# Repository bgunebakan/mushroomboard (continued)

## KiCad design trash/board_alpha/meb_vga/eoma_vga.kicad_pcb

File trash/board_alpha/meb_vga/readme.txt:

http://www.gplsquared.com/eoma_boot/vga_2013_08_18.tar.gz

This is to create a VGA interface for EOMA68 Micro Engineering Board

The creative designs here are subject to copyright (C) J. Michael 2013,
and contributors, and all released under GPL 3 license.
You can obtain a copy of the license from http://www.fsf.org

The PCB has been done up for Seeed Studio manufacturing requirements.
There is also eoma_vga_panel.kicad_pcb which has 4 panelized copies inside
a 10cm x 10cm boundary to suit Seeed Studio manufacturing.

If you make a board I'm happy to put put it up as an example board that
others have made.
Send photo by email to research@enemygadgets.com.

Bug fixes for this release:
1. VGA footprint hole diamters to 30 mil
2. SMD electrolytic capacitor 3D orientation repaired
3. Added extra capacitors for decoupling VAA line
4. Added a filter network to power line to prevent RF leaking out that way.
5. Added 1206 ferrite beads (use any off the shelf 1206 size ferrite bead).
6. Repaired wiring for Vref, SYNC and BLANK and got rid of some components.
7. Reparied wiring for VGA gnd connection.
8. Rewired parts of the DIL 22x2 connector.

Previous version :  http://www.gplsquared.com/eoma_boot/vga_2013_08_18.tar.gz

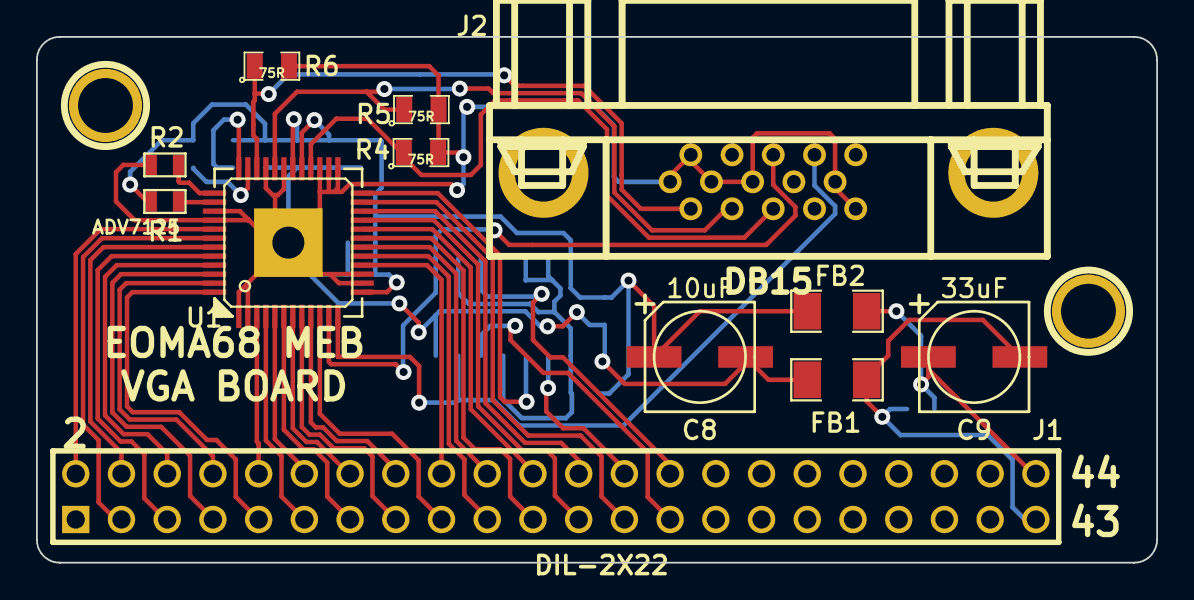
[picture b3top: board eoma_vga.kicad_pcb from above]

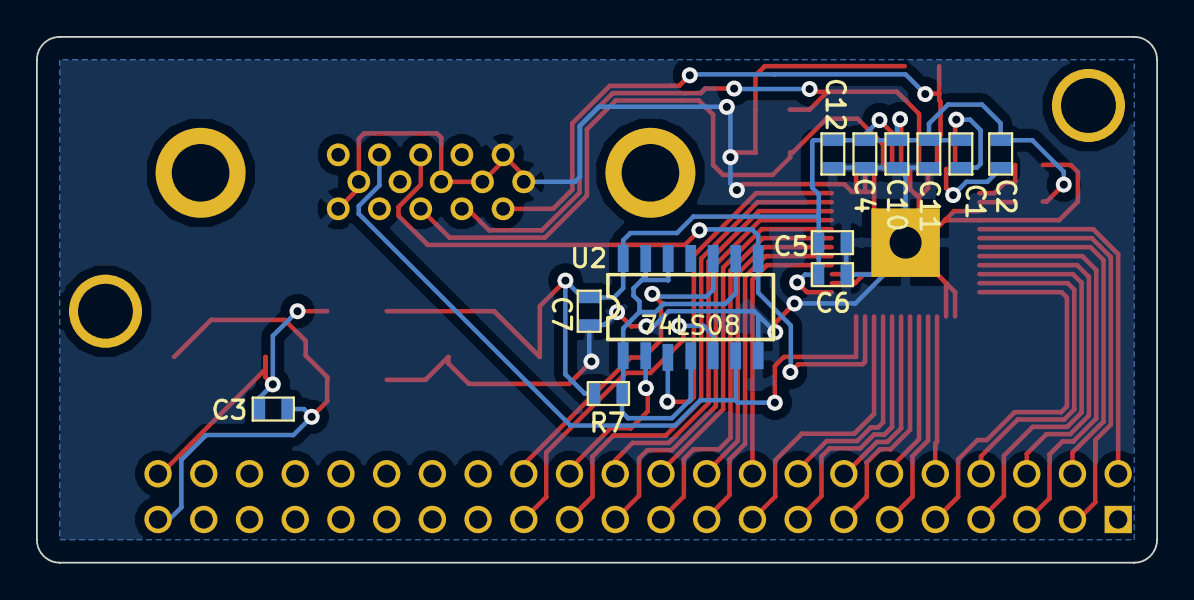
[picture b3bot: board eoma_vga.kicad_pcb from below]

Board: 2 copper layers, 62.2 x 29.2 mm, 24 parts (12 on the bottom side), 42 nets.

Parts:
C1, C2, C3, C4, C5, C7, C11: 0.1uF; SM0603
C6, C10, C12: 0.01uF; SM0603
C8: 10uF; SMD_ELECTROLYTIC_250r
C9: 33uF; SMD_ELECTROLYTIC_250r
FB1, FB2: 1206 ferrite bead; SM1206
J1: DIL-2X22; PIN_ARRAY_22X2
J2: DB15; DB_15F-VGA
R1, R7: 1K; SM0603
R2: 530R; SM0603
R4, R5, R6: 75R; SM0805
U1: ADV7125; lqfp48
U2: 74LS08; SOIC-14_Narrow

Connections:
+5V: C1.2, C2.2, C4.2, C5.2, C6.2, C7.2, C8.1, C10.2, C11.2, C12.2, FB2.1, R1.1, R7.1, U1.13, U1.29, U1.30, U2.14
GND: C4.1, C5.1, C6.1, C7.1, C8.2, C10.1, C11.1, C12.1, FB1.1, J2.5, J2.6, J2.7, J2.8, J2.10, J2.11, R2.2, R4.2, R5.2, R6.2, U1.1, U1.2, U1.14, U1.15, U1.25, U1.26, U1.27, U1.31, U1.33, U1.39, U1.40, U1.49, U2.7
unnamed: J1.2, U1.41
unnamed: J1.5, U1.44
unnamed: J1.12, U1.5
unnamed: J1.10, U1.3
unnamed: J1.9, U1.48
unnamed: J1.7, U1.46
unnamed: J1.3, U1.42
unnamed: J1.8, U1.47
unnamed: J1.6, U1.45
unnamed: J1.4, U1.43
unnamed: J1.26, U2.2
unnamed: R2.1, U1.37
unnamed: J1.27, U2.5
unnamed: J1.28, U2.10
unnamed: U1.24, U2.3
unnamed: C2.1, U1.35
unnamed: C1.1, U1.36
unnamed: R1.2, U1.38
unnamed: J1.25, U1.23
unnamed: J2.13, U1.11, U2.8
unnamed: J1.20, U1.18
unnamed: J1.18, U1.16
unnamed: J1.17, U1.10
unnamed: J1.15, U1.8
unnamed: J1.13, U1.6
unnamed: J1.11, U1.4
unnamed: J1.16, U1.9
unnamed: J1.14, U1.7
unnamed: J1.19, U1.17
unnamed: J1.23, U1.21
unnamed: J1.21, U1.19
unnamed: J1.24, U1.22
unnamed: J1.22, U1.20
unnamed: J2.2, R5.1, U1.32
unnamed: J2.1, R6.1, U1.34
unnamed: J2.3, R4.1, U1.28
unnamed: J2.14, U1.12, U2.6
unnamed: C3.1, C9.2, FB1.2, J1.43
unnamed: C3.2, C9.1, FB2.2, J1.44
unnamed: R7.2, U2.1, U2.4, U2.9, U2.12, U2.13

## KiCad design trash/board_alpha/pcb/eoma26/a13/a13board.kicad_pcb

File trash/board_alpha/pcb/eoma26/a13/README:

Copyright (C) 2013 Sergey Lapin
Copyright (C) 2013 Luke Kenneth Casson Leighton <lkcl@qimod.com>

These schematics and PCB layout are free: you can redistribute it
and/or modify it under the terms of the GNU General Public License
as published by the Free Software Foundation, either version 3
of the License, or (at your option) any later version.

This schematic and PCB layout are distributed in the hope that these
will be useful, but WITHOUT ANY WARRANTY; without even the implied
warranty of MERCHANTABILITY or FITNESS FOR A PARTICULAR PURPOSE.
See the GNU General Public License for more details.

You should have received a copy of the GNU General Public License
along with this program.  If not, see <http://www.gnu.org/licenses/>.

Please note, that this license is only for schematics and board layout,
and symbol libraries.
I don't know, and I don't want to know of any patent issues you can get
into using this design. Good luck.

Also, `sexpdata` is licensed under the terms of the BSD 2-Clause License.
See the source code for more information.

Symbol for Allwinner A13 was taken from Olimex PCB for OLinuXino,
and is subject to their license and permissions.
See https://github.com/OLIMEX/OLINUXINO

S.

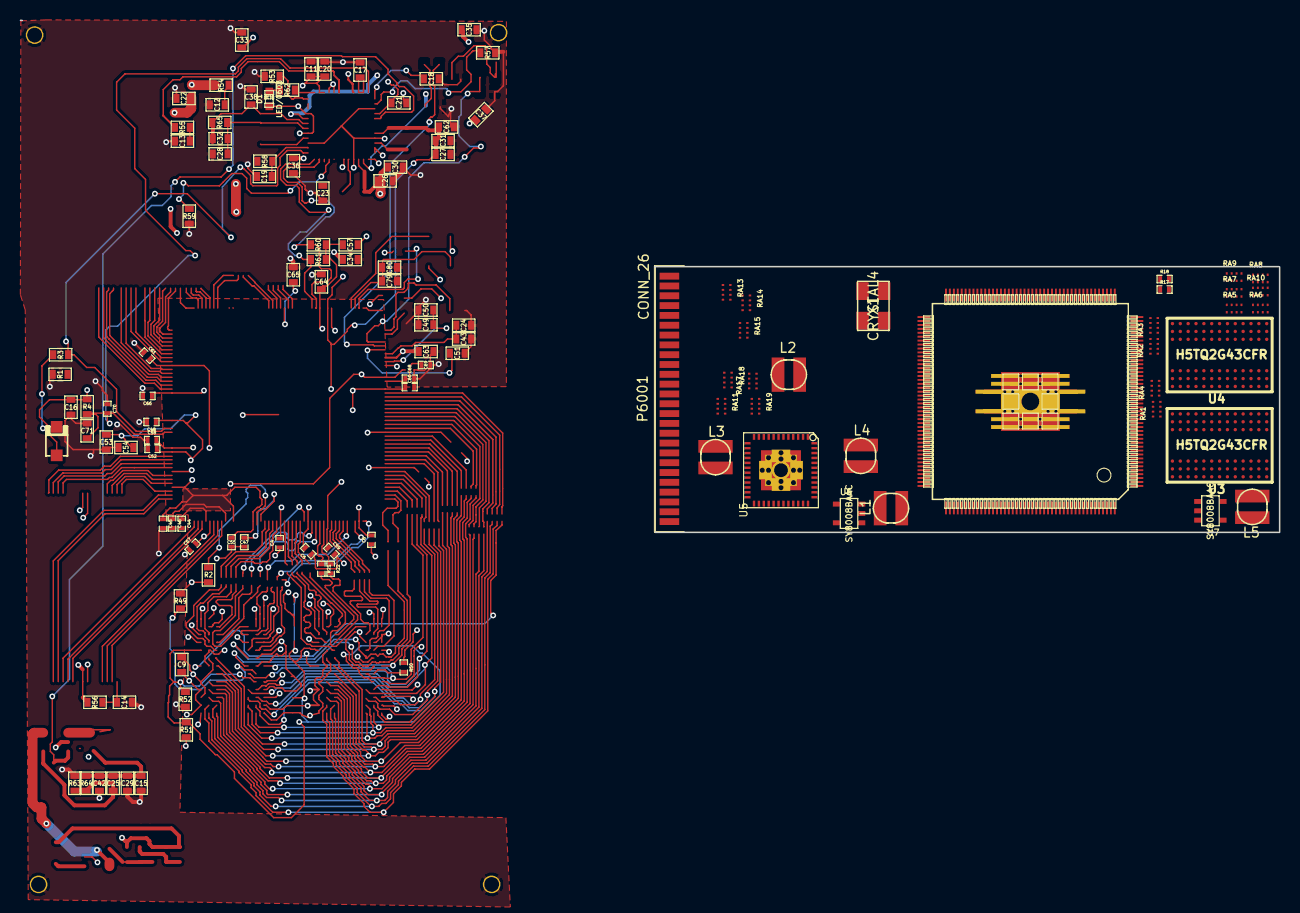
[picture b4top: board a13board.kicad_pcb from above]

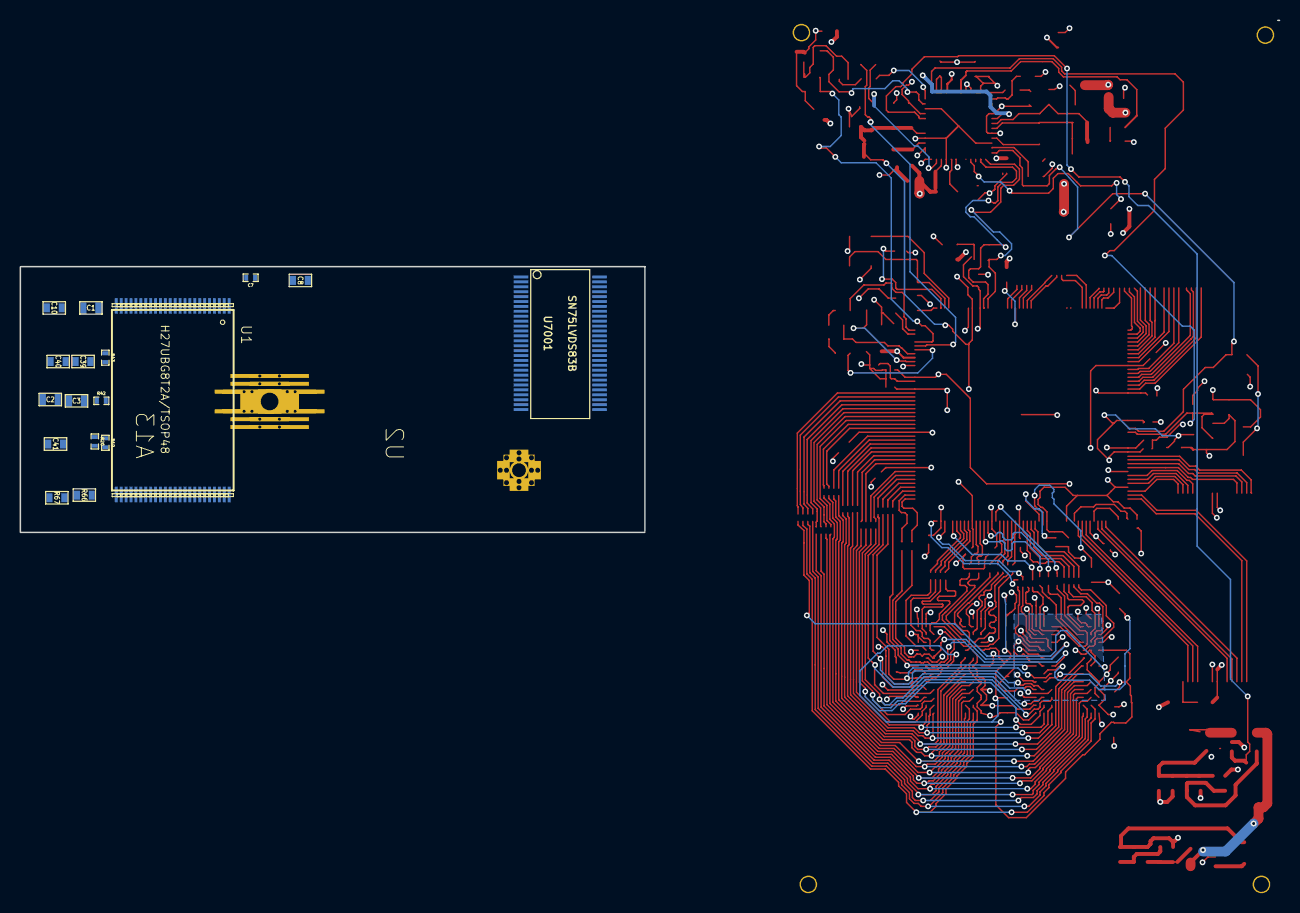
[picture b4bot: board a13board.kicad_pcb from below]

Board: 6 copper layers, 128.2 x 52.1 mm, 141 parts (17 on the bottom side), 236 nets.

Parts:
C1, C2, C3: 100nF; SM0603_Capa
C4, C5, C6, C7, C45, C47, C52, C55, C60, C61, C67, C69: 100nF; SM0402
C8, C9, C10, C15, C43, C50, C54, C57, C64, C65, C71: 100nF; SM0603A
C11, C12, C13, C20, C21, C22, C23, C24, C26, C27, C28, C33, C34, C35, C36, C37, C38, C49, C53, C62: 10uF/6.3V; SM0603A
C14: NA(100nF); SM0603A
C16: NA(22uF/6.3V); SM0603A
C17, C18, C32, C51: 1uF; SM0603A
C19, C30, C31: 1nF; SM0603A
C25: 47pF; SM0603A
C29, C40, C41, C42, C63: 22uF/6.3V; SM0603A
C39: 22pF; SM0603A
C44, C58, C66: 22uF/6.3V; SM0402
C46, C48, C59, C68: 10uF/6.3V; SM0402
C70: 1uF; SM0402
C79, C80: 33pF; SM0603A
D1: LED/0603; LED-0603
D2: 1N5819(S4SOD-123); SOD123
L1, L2, L3, L4, L5: 2.2uH/1.5A/DCR<0.1R/CD32; CD32
P6, P7, P8, P9: CONN_1; 1pin
P6001: CONN_26; EOMA-26
R1, R57: 200k/1%; SM0603A
R2, R49, R53: 240R/1%; SM0603A
R3, R4: 47k; SM0603A
R17, R18, R19, R20, R21, R22, R42, R43: 22R; SM0402
R50: 240R/1%; SM0402
R51, R52: 2k/1%; SM0603A
R54, R55: 1R; SM0603A
R56: NA(10k); SM0603A
R58, R59, R60, R61, R62: 2.2k; SM0603A
R63: 22k/1%; SM0603A
R64: 100k/1%; SM0603A
R65: 0.03R/1%; SM0603A
R66: 3.3k/1%; SM0603A
R67: 4.99k/1%; SM0603A
RA1, RA2, RA3, RA4, RA5, RA6, RA7, RA8, RA9, RA10, RA11, RA13, RA14, RA15, RA17, RA18, RA19: RA4X0402; RN4x0402
U1: H27UBG8T2A/TSOP48; TSOP48
U2: A13; allwinner_a13-OLIMEX_IC_TQFP176
U3, U4: H5TQ2G43CFR; BGA78
U5: OLIMEX_IC_AXP209; QFN48+1
U6, U7: SY8008BAAC; SOT23-5
U7001: SN75LVDS83B; TSSOP-56
X1: CRYSTAL4; C5032

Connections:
5V_EXT: R54.2, U5.32, U5.33
5V_OTG: R55.2, U5.31
+3.3V: C15.1, C16.1, C25.2, C29.2, C42.2, C57.2, C58.1, C61.1, C64.1, C67.1, D2.1, L1.2, R4.1, R56.1, R60.1, R61.1, R64.2, U1.12, U1.37, U2.5, U2.97, U2.100, U2.142, U2.163
/DRAM/CPU_A0: RA5.1, U2.64
/DRAM/CPU_A1: RA6.3, U2.52
/DRAM/CPU_A2: RA8.3, U2.66
/DRAM/CPU_A3: RA8.4, U2.65
/DRAM/CPU_A4: RA6.4, U2.51
/DRAM/CPU_A5: RA8.2, U2.67
/DRAM/CPU_A6: RA6.2, U2.54
/DRAM/CPU_A7: RA10.2, U2.71
/DRAM/CPU_A8: RA6.1, U2.55
/DRAM/CPU_A9: RA10.4, U2.69
/DRAM/CPU_A10: RA7.3, U2.48
/DRAM/CPU_A11: RA9.4, U2.56
/DRAM/CPU_A12: RA7.1, U2.50
/DRAM/CPU_A13: RA8.1, U2.68
/DRAM/CPU_A14: RA9.3, U2.57
/DRAM/CPU_BA0: RA5.2, U2.63
/DRAM/CPU_BA1: RA7.2, U2.49
/DRAM/CPU_BA2: RA5.3, U2.61
/DRAM/CPU_CAS: RA9.1, U2.59
/DRAM/CPU_CK: R17.2, U2.45
/DRAM/CPU_CKE: RA7.4, U2.47
/DRAM/CPU_CK_N: R18.2, U2.46
/DRAM/CPU_D0: RA1.1, U2.22
/DRAM/CPU_D1: RA3.4, U2.40
/DRAM/CPU_D2: RA1.2, U2.21
/DRAM/CPU_D3: RA3.3, U2.41
/DRAM/CPU_D4: RA1.4, U2.19
/DRAM/CPU_D5: RA3.1, U2.44
/DRAM/CPU_D6: RA1.3, U2.20
/DRAM/CPU_D7: RA3.2, U2.42
/DRAM/CPU_D8: RA2.3, U2.37
/DRAM/CPU_D9: RA4.3, U2.25
/DRAM/CPU_D10: RA2.1, U2.39
/DRAM/CPU_D11: RA4.4, U2.24
/DRAM/CPU_D12: RA2.4, U2.36
/DRAM/CPU_D13: RA4.2, U2.26
/DRAM/CPU_D14: RA2.2, U2.38
/DRAM/CPU_D15: RA4.1, U2.27
/DRAM/CPU_DM0: R42.1, U2.29
/DRAM/CPU_DM1: R43.1, U2.28
/DRAM/CPU_DQS0: R19.2, U2.31
/DRAM/CPU_DQS0_N: R20.2, U2.32
/DRAM/CPU_DQS1: R21.2, U2.33
/DRAM/CPU_DQS1_N: R22.2, U2.34
/DRAM/CPU_MEMRST: RA10.3, U2.70
/DRAM/CPU_ODT: RA10.1, U2.72
/DRAM/CPU_RAS: RA9.2, U2.58
/DRAM/CPU_WE: RA5.4, U2.60
/DRAM/DDR3_A0: RA5.8, U3.K3, U4.K3
/DRAM/DDR3_A1: RA6.6, U3.L7, U4.L7
/DRAM/DDR3_A2: RA8.6, U3.L3, U4.L3
/DRAM/DDR3_A3: RA8.5, U3.K2, U4.K2
/DRAM/DDR3_A4: RA6.5, U3.L8, U4.L8
/DRAM/DDR3_A5: RA8.7, U3.L2, U4.L2
/DRAM/DDR3_A6: RA6.7, U3.M8, U4.M8
/DRAM/DDR3_A7: RA10.7, U3.M2, U4.M2
/DRAM/DDR3_A8: RA6.8, U3.N8, U4.N8
/DRAM/DDR3_A9: RA10.5, U3.M3, U4.M3
/DRAM/DDR3_A10: RA7.6, U3.H7, U4.H7
/DRAM/DDR3_A11: RA9.5, U3.M7, U4.M7
/DRAM/DDR3_A12: RA7.8, U3.K7, U4.K7
/DRAM/DDR3_A13: RA8.8, U3.N3, U4.N3
/DRAM/DDR3_A14: RA9.6, U3.N7, U4.N7
/DRAM/DDR3_BA0: RA5.7, U3.J2, U4.J2
/DRAM/DDR3_BA1: RA7.7, U3.K8, U4.K8
/DRAM/DDR3_BA2: RA5.6, U3.J3, U4.J3
/DRAM/DDR3_CAS: RA9.8, U3.G3, U4.G3
/DRAM/DDR3_CK: R17.1, U3.F7, U4.F7
/DRAM/DDR3_CKE: RA7.5, U3.G9, U4.G9
/DRAM/DDR3_CK_N: R18.1, U3.G7, U4.G7
/DRAM/DDR3_D0: RA1.8, U3.B3
/DRAM/DDR3_D1: RA3.5, U3.C7
/DRAM/DDR3_D2: RA1.7, U3.C2
/DRAM/DDR3_D3: RA3.6, U3.C8
/DRAM/DDR3_D4: RA1.5, U3.E3
/DRAM/DDR3_D5: RA3.8, U3.E8
/DRAM/DDR3_D6: RA1.6, U3.D2
/DRAM/DDR3_D7: RA3.7, U3.E7
/DRAM/DDR3_D8: RA2.6, U4.C8
/DRAM/DDR3_D9: RA4.6, U4.D2
/DRAM/DDR3_D10: RA2.8, U4.E8
/DRAM/DDR3_D11: RA4.5, U4.E3
/DRAM/DDR3_D12: RA2.5, U4.C7
/DRAM/DDR3_D13: RA4.7, U4.C2
/DRAM/DDR3_D14: RA2.7, U4.E7
/DRAM/DDR3_D15: RA4.8, U4.B3
/DRAM/DDR3_DM0: R42.2, U3.B7
/DRAM/DDR3_DM1: R43.2, U4.B7
/DRAM/DDR3_DQS0: R19.1, U3.C3
/DRAM/DDR3_DQS0_N: R20.1, U3.D3
/DRAM/DDR3_DQS1: R21.1, U4.C3
/DRAM/DDR3_DQS1_N: R22.1, U4.D3
/DRAM/DDR3_ODT: RA10.8, U3.G1, U4.G1
/DRAM/DDR3_RAS: RA9.7, U3.F3, U4.F3
/DRAM/DDR3_RST: RA10.6, U3.N2, U4.N2
/DRAM/DDR3_WE: RA5.5, U3.H3, U4.H3
/NAND/NALE: U1.17, U2.7
/NAND/NAND_WP: C14.1, R56.2, U1.19
/NAND/NCE0: U1.9, U2.2
/NAND/NCE1: U1.10, U2.3
/NAND/NCLE: U1.16, U2.6
/NAND/NDQ0: U1.29, U2.174
/NAND/NDQ1: U1.30, U2.172
/NAND/NDQ2: U1.31, U2.171
/NAND/NDQ3: U1.32, U2.170
/NAND/NDQ4: U1.41, U2.168
/NAND/NDQ5: U1.42, U2.167
/NAND/NDQ6: U1.43, U2.166
/NAND/NDQ7: U1.44, U2.165
/NAND/NRB0: U1.7, U2.176
/NAND/NRB1: U1.6, U2.175
/NAND/NRE: U1.8, U2.1
/NAND/NWE: U1.18, U2.8
/power/VDD_CPU: C26.2, C30.2, C44.2, C45.2, C46.2, C47.2, C48.2, C52.2, C53.2, C54.2, L2.2, U2.4, U2.9, U2.11, U2.16, U2.156, U2.164, U2.169, U2.173, U5.10
/power/VDD_INT: C27.2, C31.2, C59.2, C60.2, C62.2, C65.2, C66.2, L3.2, U2.35, U2.73, U2.98, U2.109, U2.149, U5.17
CLKOUTM: P6001.18, U7001.40
CLKOUTP: P6001.19, U7001.39
EXTEN: U5.20, U6.1
GND: C1.2, C2.2, C4.2, C5.2, C6.2, C7.2, C8.2, C9.2, C10.2, C11.1, C12.1, C13.1, C14.2, C15.2, C16.2, C17.1, C18.1, C19.1, C20.1, C21.2, C22.2, C23.2, C24.1, C26.1, C27.1, C28.1, C29.1, C30.1, C31.1, C33.2, C34.2, C35.2, C36.2, C37.2, C38.1, C40.1, C41.1, C42.1, C43.1, C44.1, C45.1, C46.1, C47.1, C48.1, C49.1, C50.1, C51.2, C52.1, C53.1, C54.1, C58.2, C59.1, C60.1, C61.2, C62.1, C63.2, C64.2, C65.1, C66.1, C67.2, C68.1, C69.1, C70.2, C71.2, C79.1, C80.1, P6.1, P7.1, P8.1, P9.1, P6001.1, P6001.10, R1.1, R49.2, R50.2, R52.2, R53.1, R57.1, R59.1, R63.1, R66.1, U1.13, U1.36, U2.79, U2.GND, U3.A1, U3.A8, U3.B1, U3.B2, U3.B8, U3.C9, U3.D1, U3.D8, U3.D9, U3.F2, U3.F8, U3.H2, U3.J1, U3.J9, U3.L1, U3.L9, U3.N1, U3.N9, U4.A1, U4.A8, U4.B1, U4.B2, U4.B8, U4.C9, U4.D1, U4.D8, U4.D9, U4.F2, U4.F8, U4.H2, U4.J1, U4.J9, U4.L1, U4.L9, U4.N1, U4.N9, U5.9, U5.16, U5.22, U5.46, U6.2, U7.2, U7001.4, U7001.5, U7001.6, U7001.13, U7001.15, U7001.19, U7001.21, U7001.25, U7001.29, U7001.33, U7001.35, U7001.36, U7001.43, U7001.49, U7001.51, U7001.52, U7001.53, X1.2, X1.4
IPSOUT: C11.2, C20.2, C21.1, C22.1, C23.1, C36.1, D1.1, P6001.6, U5.7, U5.13, U5.14, U5.21, U5.34, U5.35, U5.40, U5.44, U6.4, U7.4
LCD_CLK: RA18.6, U7001.31
LCD_DE: RA18.5, U7001.30
LCD_HSYNC: RA19.8, U7001.27
LCD_VSYNC: RA19.7, U7001.28
LDO4_3V3_200MA: C37.1, U5.11
unnamed: R50.1, U4.H8
unnamed: R49.1, U3.H8
unnamed: C1.1, C2.1, C3.2, C10.1, R51.2, R52.1, U3.E1, U3.J8, U4.E1, U4.J8
unnamed: C25.1, R63.2, R64.1, U6.5
unnamed: L1.1, U6.3
unnamed: C39.1, R66.2, R67.1, U7.5
unnamed: L5.1, U7.3
unnamed: C68.2, C69.2, U2.75
unnamed: D2.2, R3.1
unnamed: R2.1, U2.17
unnamed: C55.2, C57.1, R2.2
unnamed: C24.2, C43.2, R1.2, U2.82
unnamed: C51.1, U2.83
unnamed: C49.2, C50.2, U2.80
unnamed: C32.1, C38.2, R65.2, U5.42
unnamed: L3.1, U5.15
unnamed: L4.1, U5.45
unnamed: L2.1, U5.8
unnamed: C35.1, U5.41
unnamed: C18.2, U5.24
unnamed: R57.2, U5.23
unnamed: C28.2, C32.2, L4.2, R65.1, U5.43
unnamed: R53.2, U5.37
unnamed: C12.2, R54.1
unnamed: C13.2, R55.1
unnamed: R62.2, U5.36
unnamed: D1.2, R62.1
unnamed: C17.2, U5.26, U5.27
unnamed: C19.2, R58.2, U5.47
unnamed: RA11.2, U2.110
unnamed: RA11.1, U2.111
unnamed: RA19.4, U2.112
unnamed: RA19.3, U2.113
unnamed: RA11.4, U2.107
unnamed: RA11.3, U2.108
unnamed: RA15.2, U2.138
unnamed: RA13.2, U2.147
unnamed: RA19.2, U2.126
unnamed: RA15.1, U2.139
unnamed: RA14.4, U2.140
unnamed: RA14.3, U2.141
unnamed: RA14.2, U2.143
unnamed: RA14.1, U2.144
unnamed: RA13.4, U2.145
unnamed: RA13.3, U2.146
unnamed: RA13.1, U2.148
unnamed: C79.2, C80.2, U2.91, X1.1
unnamed: U2.92, X1.3
unnamed: RA18.4, U2.128
unnamed: RA19.1, U2.127
unnamed: RA18.3, U2.129
unnamed: RA18.2, U2.130
unnamed: RA18.1, U2.131
unnamed: RA17.4, U2.132
unnamed: RA17.3, U2.133
unnamed: RA17.2, U2.134
unnamed: RA17.1, U2.135
unnamed: RA15.4, U2.136
unnamed: RA15.3, U2.137
NMI_N: R3.2, U2.158, U5.48
PD2: RA13.8, U7001.54
PD3: RA13.7, U7001.55
PD4: RA13.6, U7001.56
PD5: RA13.5, U7001.3
PD6: RA14.8, U7001.50
PD7: RA14.7, U7001.2
PD10: RA14.6, U7001.7
PD11: RA14.5, U7001.11
PD12: RA15.8, U7001.12
PD13: RA15.7, U7001.14
PD14: RA15.6, U7001.8
PD15: RA15.5, U7001.10
PD18: RA17.8, U7001.20
PD19: RA17.7, U7001.22
PD20: RA17.6, U7001.23
PD21: RA17.5, U7001.24
PD22: RA18.8, U7001.16
PD23: RA18.7, U7001.18
PWM: P6001.9, U2.103
RESET: C70.1, C71.1, R4.2, U2.159, U5.25
RESET_SW2: R59.2, U5.4
SDC0_CLK: P6001.14, RA11.7
SDC0_CMD: P6001.11, RA11.8
SDC0_D0: P6001.17, RA11.6
SDC0_D1: P6001.20, RA11.5
SDC0_D2: P6001.23, RA19.6
SDC0_D3: P6001.26, RA19.5
SVREF: C55.1, U2.18
TWI0_SCK: R60.2, U2.101, U5.2
TWI0_SDA: R61.2, U2.102, U5.1
TWI2_SCK: P6001.7, U2.160
TWI2_SDA: P6001.8, U2.161
UART1_RX: P6001.5, U2.151
UART1_TX: P6001.4, U2.152
USB0-DRV: U2.155, U5.6
USB_UDM0: P6001.2, U2.93
USB_UDP0: P6001.3, U2.94
VDD_RTC: C33.1, U5.28
VMEM: C3.1, C4.1, C5.1, C6.1, C7.1, C8.1, C9.1, C39.2, C40.2, C41.2, L5.2, R51.1, R67.2, U2.23, U2.30, U2.43, U2.53, U2.62, U3.A2, U3.A9, U3.B9, U3.C1, U3.D7, U3.E2, U3.E9, U3.G2, U3.G8, U3.K1, U3.K9, U3.M1, U3.M9, U4.A2, U4.A9, U4.B9, U4.C1, U4.D7, U4.E2, U4.E9, U4.G2, U4.G8, U4.K1, U4.K9, U4.M1, U4.M9
VPP: C34.1, C63.1, U2.81, U5.12, U7.1
Y0M: P6001.24, U7001.48
Y0P: P6001.25, U7001.47
Y1M: P6001.21, U7001.46
Y1P: P6001.22, U7001.45
Y2M: P6001.15, U7001.42
Y2P: P6001.16, U7001.41
Y3M: P6001.12, U7001.38
Y3P: P6001.13, U7001.37

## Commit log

2015-03-06 todo
2015-03-09 enoki project started with kicad
2015-03-09 ethernet lib added
2015-03-13 initual commit
2015-03-24 radio shematic has done
2015-03-27 ram lib ok
2015-03-30 working on pcb
2016-07-10 unutulmuş commit
2019-10-23 Create LICENSE
